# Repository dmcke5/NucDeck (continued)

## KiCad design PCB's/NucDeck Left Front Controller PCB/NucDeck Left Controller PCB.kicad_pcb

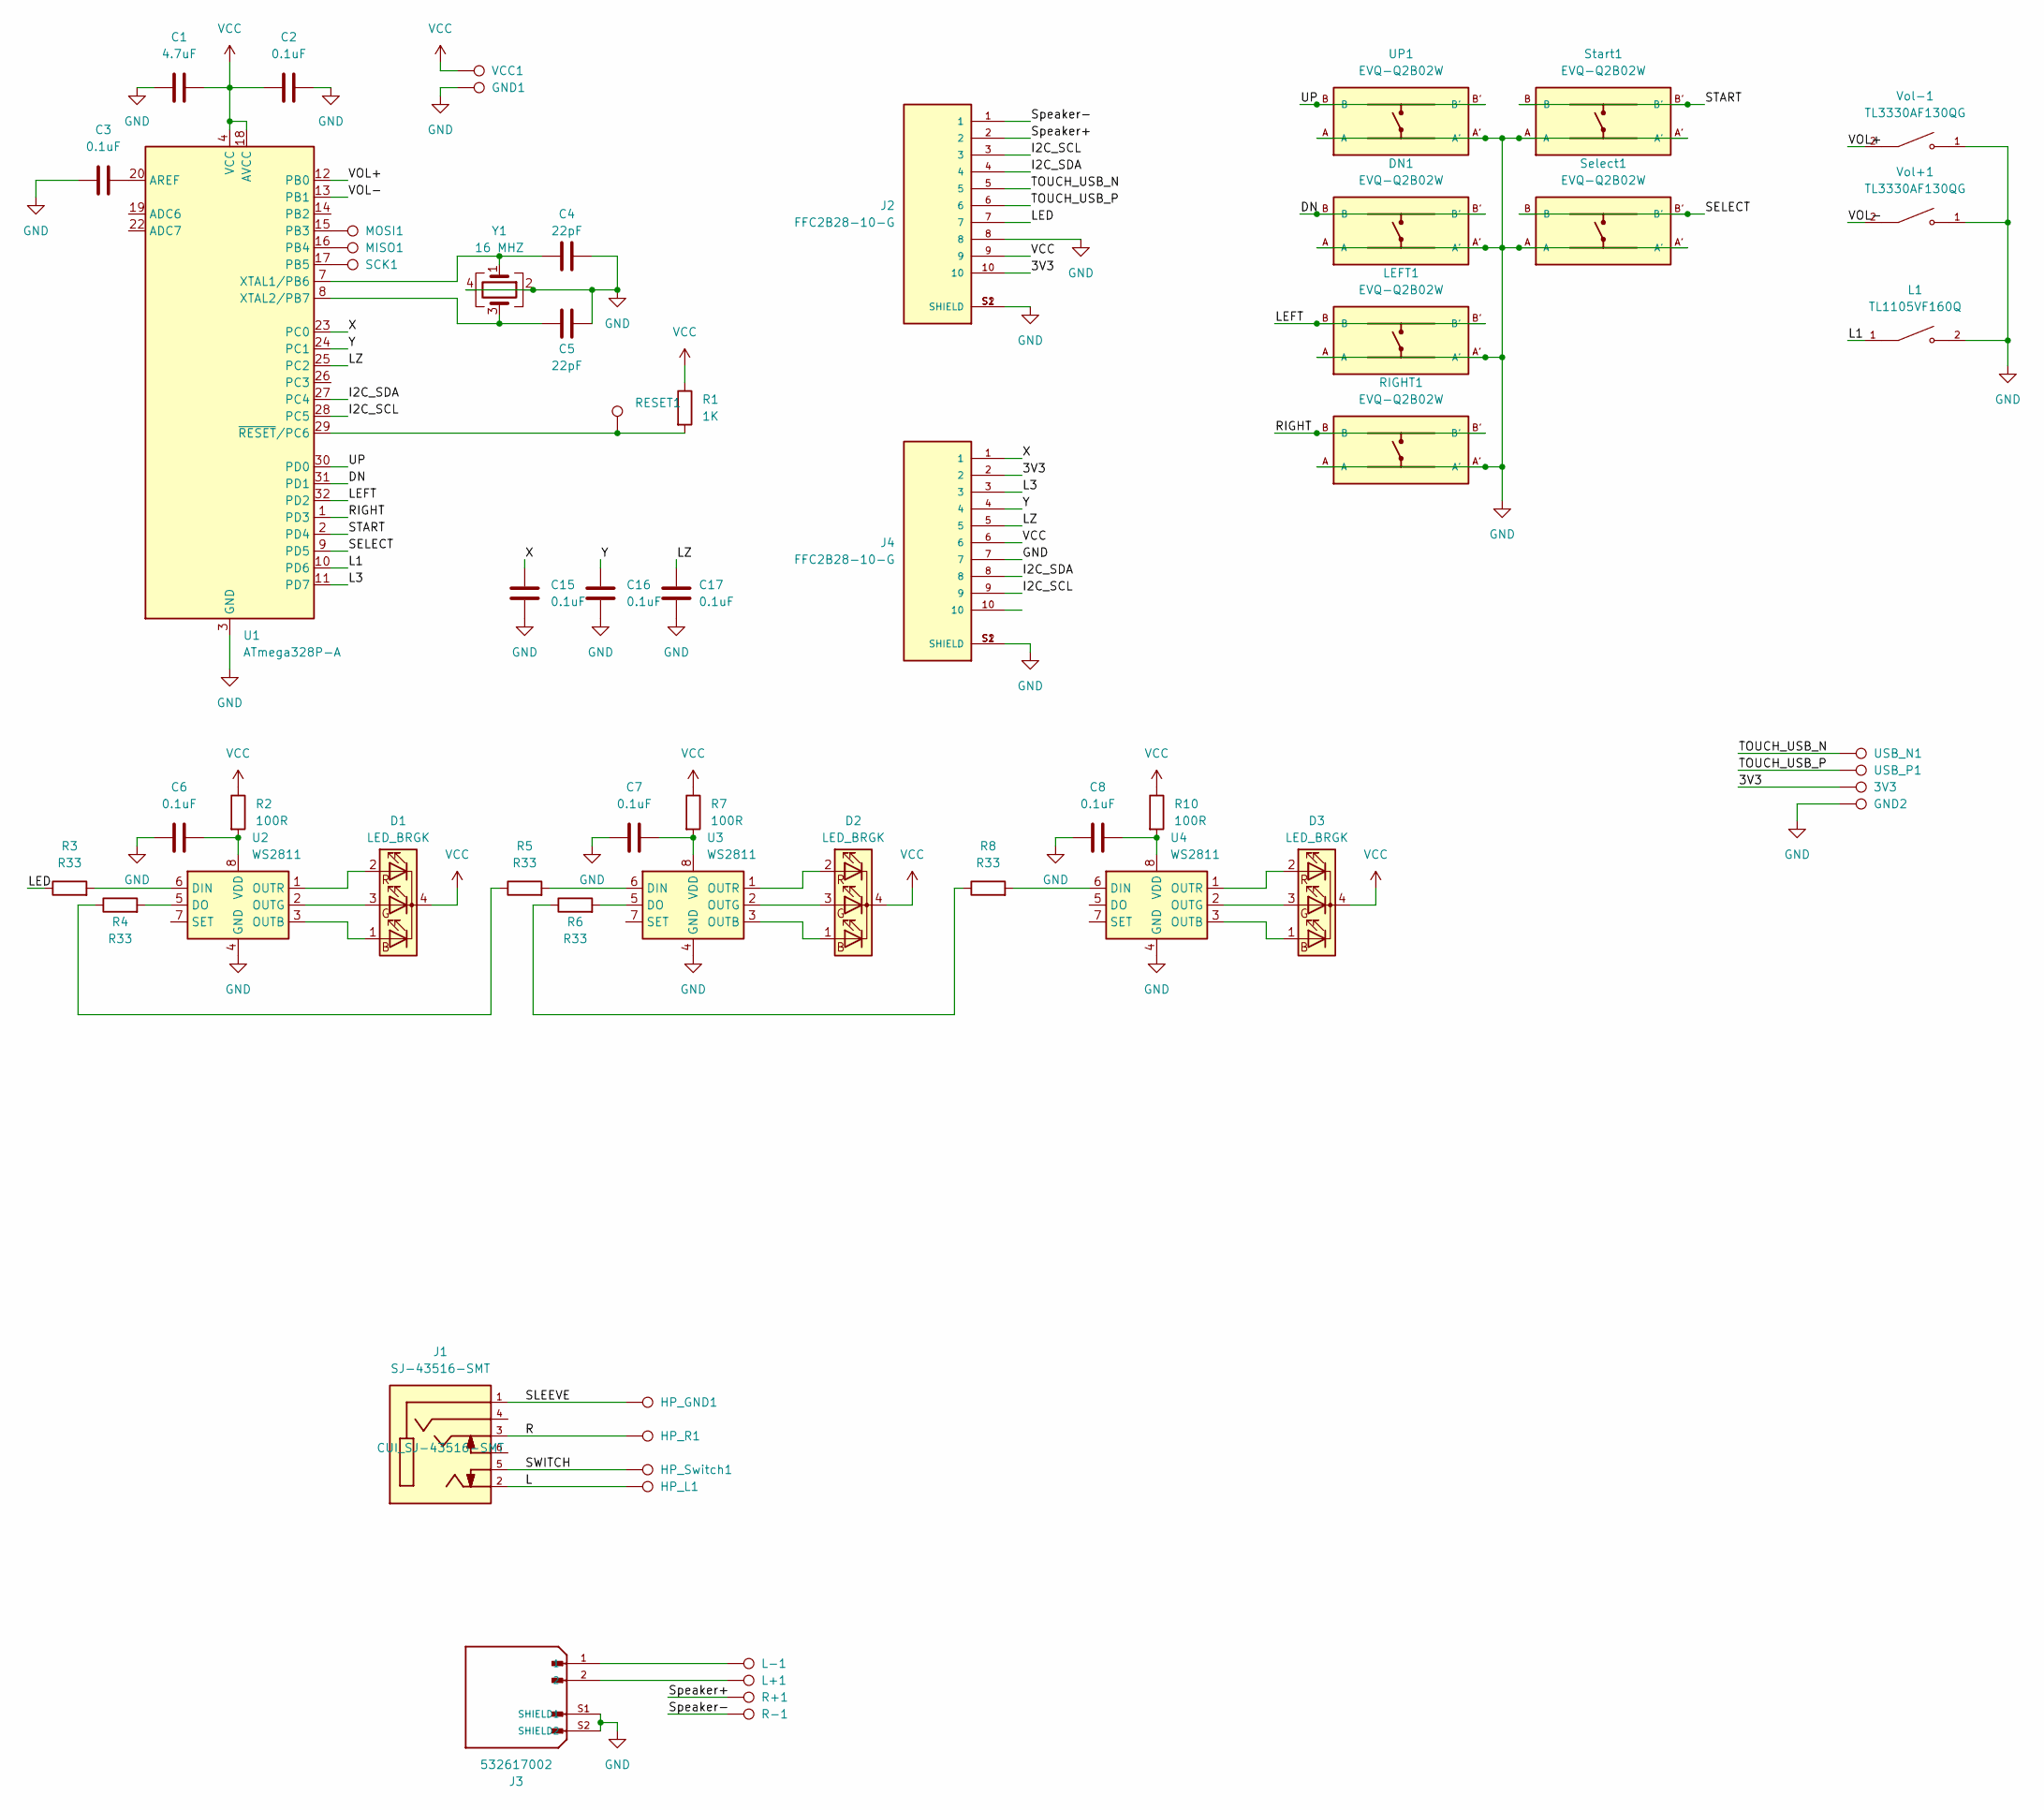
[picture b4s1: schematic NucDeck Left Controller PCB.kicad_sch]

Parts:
3V3: 3V3; TestPoint_THTPad_D1.5mm_Drill0.7mm
C1: 4.7uF; C_0603_1608Metric_Pad1.08x0.95mm_HandSolder
C2, C3, C6, C7, C8, C15, C16, C17: 0.1uF; C_0603_1608Metric_Pad1.08x0.95mm_HandSolder
C4, C5: 22pF; C_0603_1608Metric_Pad1.08x0.95mm_HandSolder
D1, D2, D3: LED_BRGK; LED_T36K3BGR-05D000121U1930
DN1: EVQ-Q2B02W; SW_EVQ-Q2B02W
GND1: GND; TestPoint_Pad_D1.5mm
GND2: GND; TestPoint_THTPad_D1.5mm_Drill0.7mm
HP_GND1: TestPoint_Pad_1.0x1.0mm
HP_L1: TestPoint_Pad_1.0x1.0mm
HP_R1: TestPoint_Pad_1.0x1.0mm
HP_Switch1: TestPoint_Pad_1.0x1.0mm
J1: SJ-43516-SMT; CUI_SJ-43516-SMT; PART_REV 1.02
J2, J4: FFC2B28-10-G; GCT_FFC2B28-10-G; PARTREV A
J3: 532617002; MOLEX_532617002; PARTREV B; DigiKey_Part_Number WM25389TR-ND
L1: TL1105VF160Q; SW_TL1105VF160Q; PARTREV C
L+1: TestPoint_Pad_1.0x1.0mm
L-1: TestPoint_Pad_1.0x1.0mm
LEFT1: EVQ-Q2B02W; SW_EVQ-Q2B02W
MISO1: MISO; TestPoint_Pad_D1.5mm
MOSI1: MOSI; TestPoint_Pad_D1.5mm
R1: 1K; R_0603_1608Metric_Pad0.98x0.95mm_HandSolder
R2, R7, R10: 100R; R_0603_1608Metric_Pad0.98x0.95mm_HandSolder
R3, R4, R5, R6, R8: R33; R_0603_1608Metric_Pad0.98x0.95mm_HandSolder
R+1: TestPoint_Pad_1.0x1.0mm
R-1: TestPoint_Pad_1.0x1.0mm
RESET1: RESET; TestPoint_Pad_D1.5mm
RIGHT1: EVQ-Q2B02W; SW_EVQ-Q2B02W
SCK1: SCK; TestPoint_Pad_D1.5mm
Select1: EVQ-Q2B02W; SW_EVQ-Q2B02W
Start1: EVQ-Q2B02W; SW_EVQ-Q2B02W
U1: ATmega328P-A; TQFP-32_7x7mm_P0.8mm
U2, U3, U4: WS2811; SOP-8_3.9x4.9mm_P1.27mm
UP1: EVQ-Q2B02W; SW_EVQ-Q2B02W
USB_N1: USB_N; TestPoint_THTPad_D1.5mm_Drill0.7mm
USB_P1: USB_P; TestPoint_THTPad_D1.5mm_Drill0.7mm
VCC1: VCC; TestPoint_Pad_D1.5mm
Vol+1: TL3330AF130QG; SW_TL3330AF130QG; PARTREV B
Vol-1: TL3330AF130QG; SW_TL3330AF130QG; PARTREV B
Y1: 16 MHZ; Crystal_SMD_5032-4Pin_5.0x3.2mm

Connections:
/3V3: 3V3.1, J2.10, J4.2
/DN: DN1.B, DN1.B', U1.31 (PD1)
/I2C_SCL: J2.3, J4.9, U1.28 (PC5)
/I2C_SDA: J2.4, J4.8, U1.27 (PC4)
/L: HP_L1.1, J1.2
/L1: L1.1, U1.10 (PD6)
/L3: J4.3, U1.11 (PD7)
/LED: J2.7, R3.1
/LEFT: LEFT1.B, LEFT1.B', U1.32 (PD2)
/LZ: C17.2, J4.5, U1.25 (PC2)
/R: HP_R1.1, J1.3
/RIGHT: RIGHT1.B, RIGHT1.B', U1.1 (PD3)
/SELECT: Select1.B, Select1.B', U1.9 (PD5)
/SLEEVE: HP_GND1.1, J1.1
/START: Start1.B, Start1.B', U1.2 (PD4)
/SWITCH: HP_Switch1.1, J1.5
/Speaker+: J2.2, R+1.1
/Speaker-: J2.1, R-1.1
/TOUCH_USB_N: J2.5, USB_N1.1
/TOUCH_USB_P: J2.6, USB_P1.1
/UP: U1.30 (PD0), UP1.B, UP1.B'
/VOL+: U1.12 (PB0), Vol-1.2
/VOL-: U1.13 (PB1), Vol+1.2
/X: C15.2, J4.1, U1.23 (PC0)
/Y: C16.2, J4.4, U1.24 (PC1)
GND: C1.1, C2.2, C3.1, C4.2, C5.2, C6.1, C7.1, C8.1, C15.1, C16.1, C17.1, DN1.A, DN1.A', GND1.1, GND2.1, J2.8, J2.11, J2.12, J2.S1 (SHIELD), J2.S2 (SHIELD), J3.S1 (SHIELD1), J3.S2 (SHIELD2), J4.7, J4.11, J4.12, J4.S1 (SHIELD), J4.S2 (SHIELD), L1.2, LEFT1.A, LEFT1.A', RIGHT1.A, RIGHT1.A', Select1.A, Select1.A', Start1.A, Start1.A', U1.3 (GND), U1.5 (GND), U1.21 (GND), U2.4 (GND), U3.4 (GND), U4.4 (GND), UP1.A, UP1.A', Vol+1.1, Vol+1.S1, Vol+1.S2, Vol-1.1, Vol-1.S1, Vol-1.S2, Y1.2, Y1.4
unnamed: D1.1 (BA), U2.3 (OUTB)
unnamed: D1.3 (GA), U2.2 (OUTG)
unnamed: D1.2 (RA), U2.1 (OUTR)
unnamed: D2.1 (BA), U3.3 (OUTB)
unnamed: D2.3 (GA), U3.2 (OUTG)
unnamed: D2.2 (RA), U3.1 (OUTR)
unnamed: D3.1 (BA), U4.3 (OUTB)
unnamed: D3.3 (GA), U4.2 (OUTG)
unnamed: D3.2 (RA), U4.1 (OUTR)
unnamed: J3.1, L-1.1
unnamed: J3.2, L+1.1
unnamed: R4.1, R5.1
unnamed: R6.1, R8.1
unnamed: C3.2, U1.20 (AREF)
unnamed: MOSI1.1, U1.15 (PB3)
unnamed: MISO1.1, U1.16 (PB4)
unnamed: SCK1.1, U1.17 (PB5)
unnamed: C4.1, U1.7 (XTAL1/PB6), Y1.1
unnamed: C5.1, U1.8 (XTAL2/PB7), Y1.3
unnamed: R1.2, RESET1.1, U1.29 (~RESET/PC6)
unnamed: R3.2, U2.6 (DIN)
unnamed: R4.2, U2.5 (DO)
unnamed: C6.2, R2.2, U2.8 (VDD)
unnamed: R5.2, U3.6 (DIN)
unnamed: R6.2, U3.5 (DO)
unnamed: C7.2, R7.2, U3.8 (VDD)
unnamed: R8.2, U4.6 (DIN)
unnamed: C8.2, R10.2, U4.8 (VDD)
VCC: C1.2, C2.1, D1.4 (K), D2.4 (K), D3.4 (K), J2.9, J4.6, R1.1, R2.1, R7.1, R10.1, U1.4 (VCC), U1.6 (VCC), U1.18 (AVCC), VCC1.1

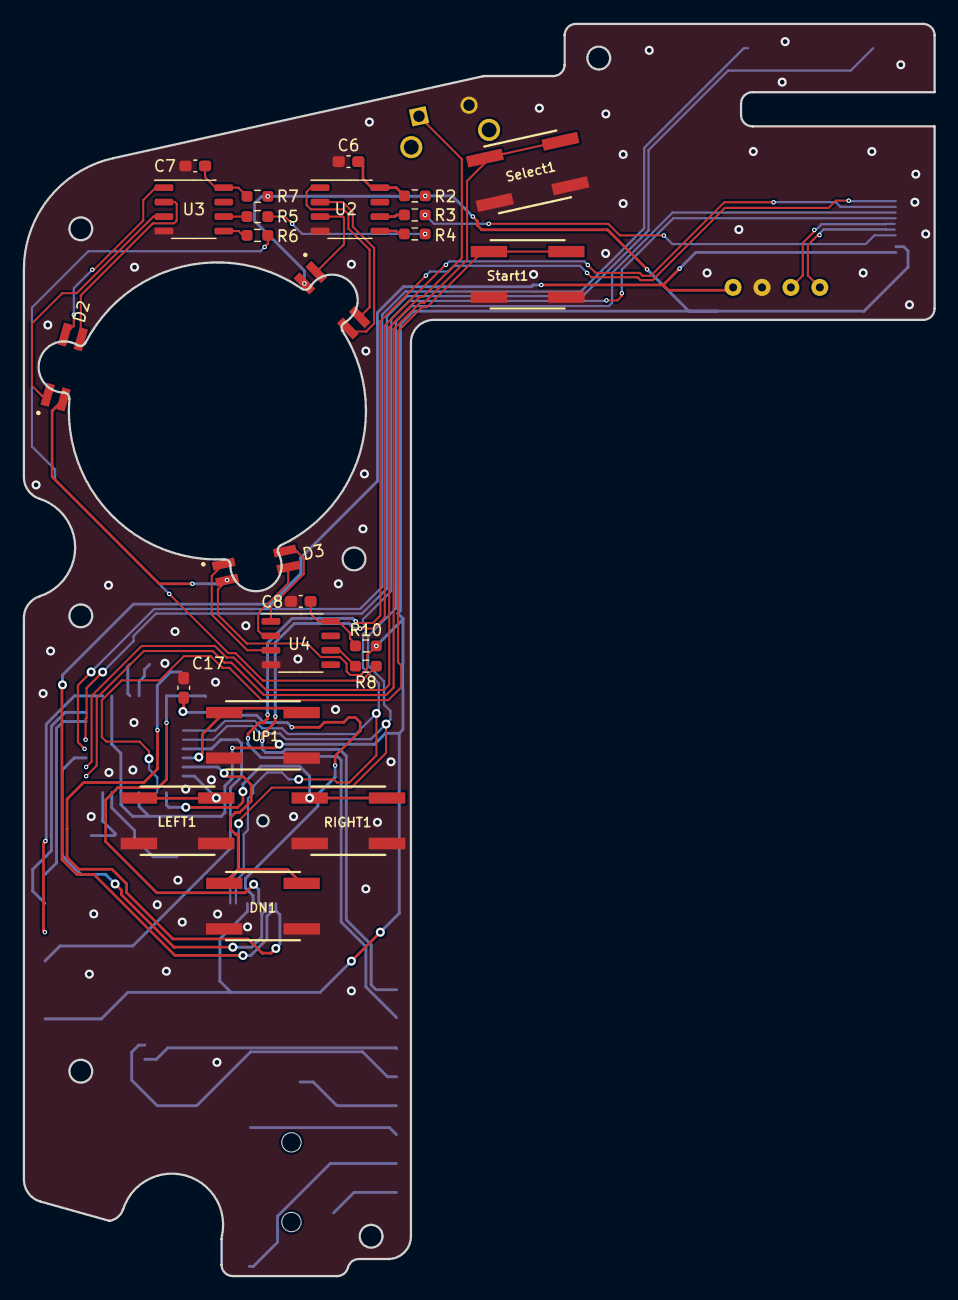
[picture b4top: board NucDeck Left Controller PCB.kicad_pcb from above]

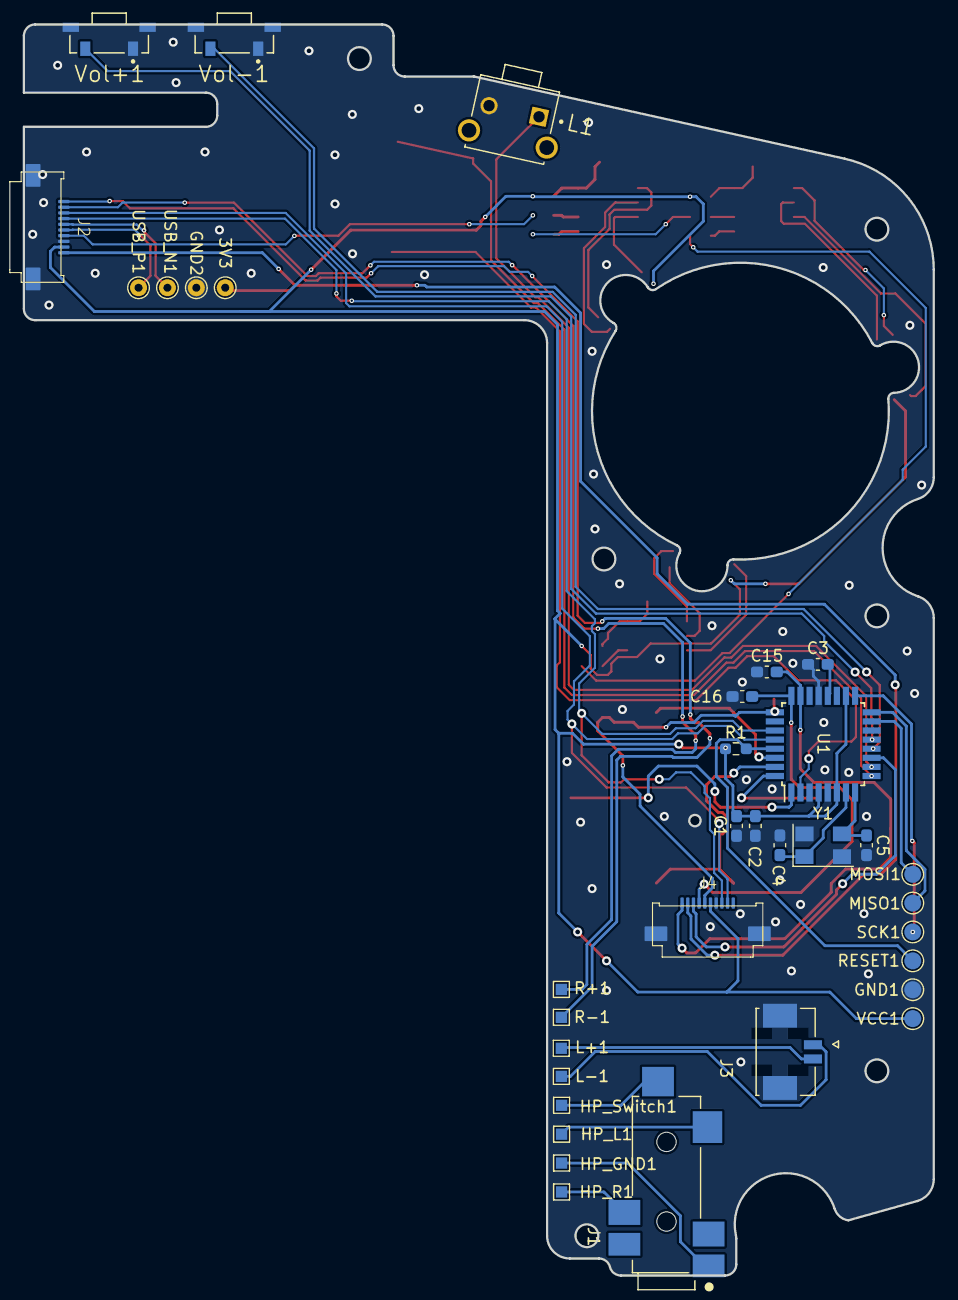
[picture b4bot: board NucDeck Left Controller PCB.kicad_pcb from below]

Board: 2 copper layers, 80.0 x 110.0 mm, 59 parts (35 on the bottom side), 55 nets.

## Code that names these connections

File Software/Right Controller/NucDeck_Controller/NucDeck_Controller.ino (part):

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
//MPU6050
const int MPU6050 = 0x68;
const byte MPU6050_SDA = 14;
const byte MPU6050_SCL = 15;
float AccX, AccY, AccZ;
float GyroX, GyroY, GyroZ;
float GyroLastX, GyroLastY, GyroLastZ;
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int ledBrightness = 255; //LED Brightness
int currentBrightness;  //Current LED Brightness
String rgbMode[2] = {"Breath","Halo"}; //LED pattern. Used in RGB Menu
int rgbModeSelect = 0;  //LED mode selected in menu
unsigned long LED_Timer;  //LED effect timer
unsigned long LED_Fadeout;  //LED fade out timer
unsigned long LED_Fadein; //LED fade in timer
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
//Controller Button setup
int buttonCount = 7;                   //Number of buttons connected to Pico
byte buttonPins[7] = {0,1,8,13,4,6,9}; //A,B,X,Y,Menu, R1, R3
byte modeSwitch = 5;                   //Digital IO of controller mode switch
int lastMode = 2;                      //Last controller mode displayed. Used for display updates. 0 = Controller Mode, 1 = Keyboard Mode, 2 = Initialised

//Menu Variables
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bool rgbMenu = false;             //Set to true to open RGB menu
bool batteryMenu = false;         //Set to true to open Battery menu
boolean calibrationMode = false;  //Set to true to open Calibration menu
int menuSelected = 0;             //which menu item is highlighted
int menuOptions = 7;              //Number of Items in Menu List
String mainMenu[7] = {"Aim Assist","Calibrate", "Battery", "RGB", "Settings", "ALT F4", "ESC"}; //Main Menu titles
bool aimAssist = true;            //If aim assist is enabled. NOT YET IMPLEMENTED
bool shutdownMode = false;        //Set to true if shutdown is initiated
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  for(int i = 0; i < buttonCount; i++){ //Set all button pins as input pullup. Change to INPUT if using external resistors.
    pinMode(buttonPins[i], INPUT_PULLUP);
  }
  pinMode(modeSwitch, INPUT_PULLUP);  //Turn on pullup for mode switch
  pinMode(28, INPUT); //Set input for right trigger
  pinMode(27, INPUT); //Set input for right joystick X
  pinMode(26, INPUT); //Set input for right joystick Y

  //PC Power Switch
  pinMode(3, OUTPUT); //Setup power switch pin as an output
  digitalWrite(3, LOW);  //Set output low so power doesn't switch off immediately 

  Serial.begin(9600); //Begin serial connection. Uncomment following two lines for debugging to ensure serial has connected before output begins.
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
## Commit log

2023-07-28 Create Licence
2023-07-30 Create blank
2023-07-30 Move Files to folder
2023-07-30 Add STLs
2023-07-30 Add Parts List
2023-07-30 Parts list updated
2023-07-30 Update Parts List
2023-07-30 Updated Different Versions of buttons
2023-08-07 Updated files
2023-08-09 Added Files
2023-08-09 Readme Update
2023-08-11 Upload Test Print
2023-08-19 Update README.md
    Added latest video link to readme
2023-09-18 Added STL for joystick surround rings
2023-09-18 Added trigger buttons
2024-01-07 Controller PCB's
2024-02-29 Update Title Image
2024-03-22 Added BMS and Controller Software
2024-04-12 Update NucDeck Left Top Controller BMS PCB - Rev 1.1.csv
    Update inductor part number
2024-04-12 Update NucDeck Left Top Controller BMS PCB - Rev 1.1.csv
    Update Sense Resistor Part Number
2024-04-13 Update README.md
    Added cost to build
    Added battery cell balancer to list
2024-04-13 Update README.md
    tidying up
2024-04-13 Update README.md
    Added price breakdown
2024-07-31 Update README.md
    Updated lipo cell balancer link
